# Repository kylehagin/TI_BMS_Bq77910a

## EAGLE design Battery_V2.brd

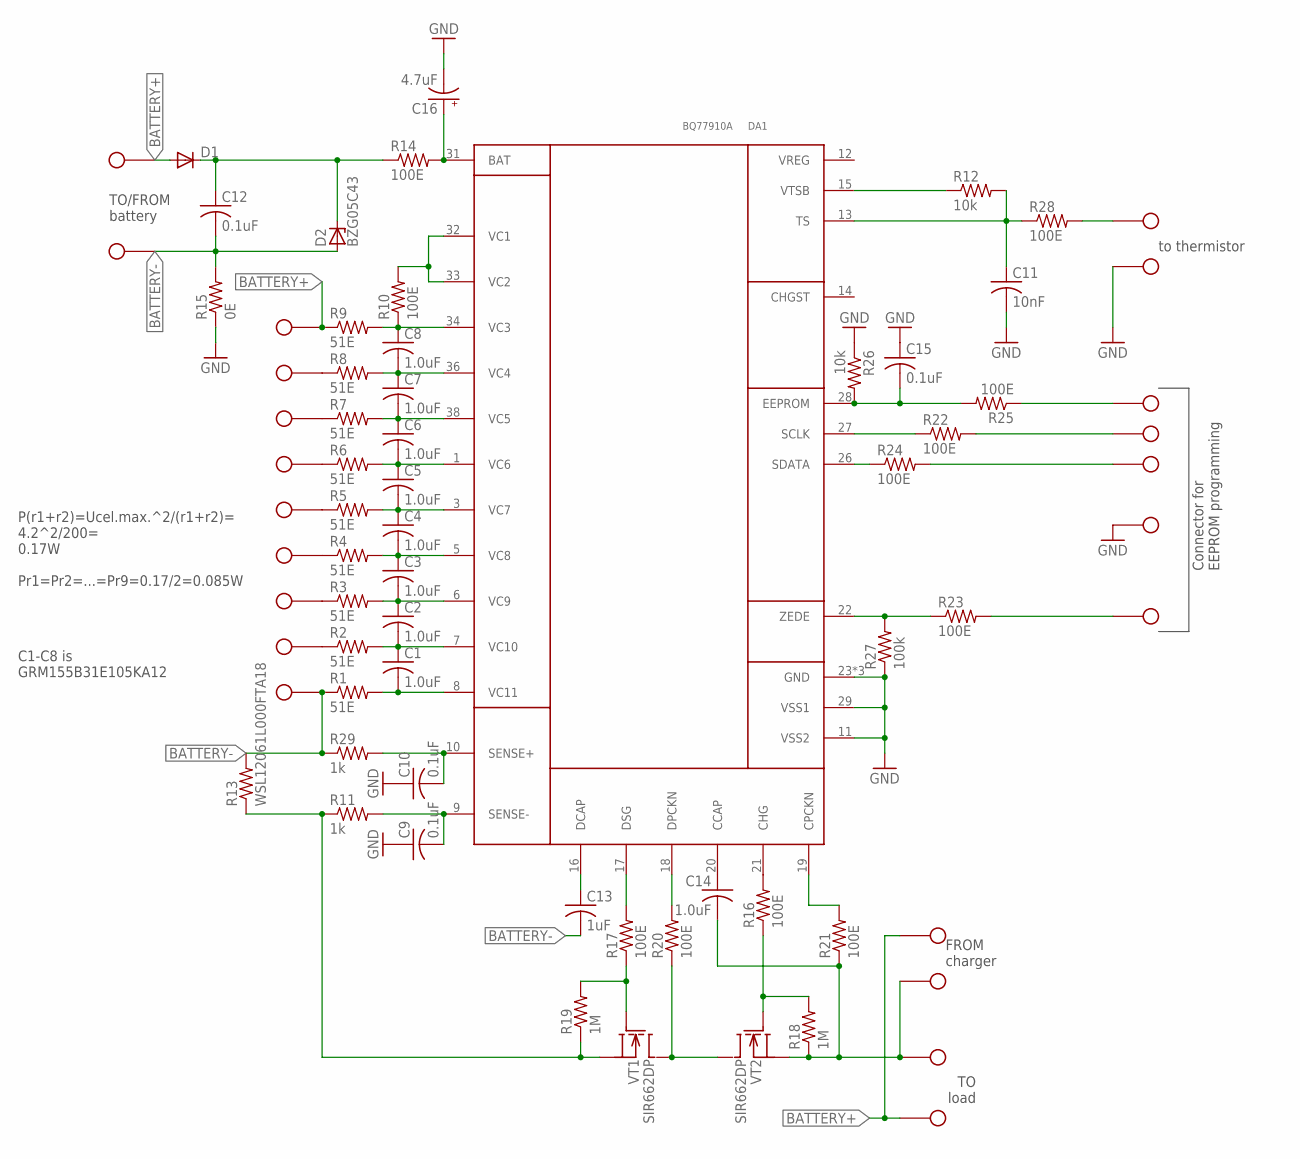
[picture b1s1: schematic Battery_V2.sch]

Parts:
C1, C2, C3, C4, C5, C6, C7, C8: 1.0uF; C0402K
C9, C10: 0.1uF; C0201
C11: 10nF; C0201
C12, C15: 0.1uF; C0402K
C13: 1uF; C0402K
C14: 1.0uF; C0603K
C16: 4.7uF; SMC_P
D1: DIODE-DO-214AC; DO-214AC
D2: BZG05C43; DO-214AC
DA1: BQ77910A; R-PDSO-G38
R1, R2, R3, R4, R5, R6, R7, R8, R9: 51E; M2012
R10, R14, R16, R17, R20, R21, R25: 100E; R0402
R11, R29: 1k; R0201
R12: 10k; R0201
R13: WSL12061L000FTA18; R1206
R15: 0E; R0402
R18, R19: 1M; R0402
R22, R23, R24, R28: 100E; R0201
R26: 10k; R0402
R27: 100k; R0201
VT1, VT2: SIR662DP; POWERPAK_SO8
X1, X2, X3, X4, X5, X6, X7, X8, X9, X10, X11, X21, X23: SOLDER_HOLE24AWG; SOLDER_HOLE_24
X12, X13, X14, X15: SOLDER_HOLE18AWG; SOLDER_HOLE_18
X16, X17, X18, X19, X20: SOLDER_PAD; SOLDER_PAD_SMD

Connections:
BATTERY+: D1.A, R9.1, X1.1, X11.1, X12.1, X15.1
BATTERY-: C12.2, C13.2, D2.A, R1.1, R13.2, R15.2, R29.1, X9.1, X13.1
BATTERY_+: C12.1, D1.C, D2.C, R14.1
GND: C9.1, C10.1, C11.2, C15.1, C16.-, DA1.11 (VSS2), DA1.23 (GND), DA1.24 (GND), DA1.25 (GND), DA1.29 (VSS1), R15.1, R26.1, R27.1, X20.P$1, X21.1
unnamed: C1.2, DA1.8 (VC11), R1.2
unnamed: C1.1, C2.2, DA1.7 (VC10), R2.2
unnamed: C2.1, C3.2, DA1.6 (VC9), R3.2
unnamed: C3.1, C4.2, DA1.5 (VC8), R4.2
unnamed: C4.1, C5.2, DA1.3 (VC7), R5.2
unnamed: C5.1, C6.2, DA1.1 (VC6), R6.2
unnamed: C6.1, C7.2, DA1.38 (VC5), R7.2
unnamed: C7.1, C8.2, DA1.36 (VC4), R8.2
unnamed: C8.1, DA1.34 (VC3), R9.2, R10.1
unnamed: DA1.32 (VC1), DA1.33 (VC2), R10.2
unnamed: C10.2, DA1.10 (SENSE+), R29.2
unnamed: C9.2, DA1.9 (SENSE-), R11.2
unnamed: DA1.21 (CHG), R16.2
unnamed: R11.1, R13.1, R19.1, VT1.S1 (S), VT1.S2 (S), VT1.S3 (S)
unnamed: C16.+, DA1.31 (BAT), R14.2
unnamed: R2.1, X8.1
unnamed: R3.1, X7.1
unnamed: R4.1, X6.1
unnamed: R5.1, X5.1
unnamed: R6.1, X4.1
unnamed: R7.1, X3.1
unnamed: R8.1, X2.1
unnamed: DA1.17 (DSG), R17.2
unnamed: R16.1, R18.2, VT2.G
unnamed: R17.1, R19.2, VT1.G
unnamed: R20.1, VT1.D, VT2.D
unnamed: C14.2, R18.1, R21.1, VT2.S1 (S), VT2.S2 (S), VT2.S3 (S), X10.1, X14.1
unnamed: C14.1, DA1.20 (CCAP)
unnamed: DA1.18 (DPCKN), R20.2
unnamed: DA1.19 (CPCKN), R21.2
unnamed: C13.1, DA1.16 (DCAP)
unnamed: DA1.22 (ZEDE), R23.1, R27.2
unnamed: DA1.26 (SDATA), R24.1
unnamed: DA1.27 (SCLK), R22.1
unnamed: C15.2, DA1.28 (EEPROM), R25.2, R26.2
unnamed: R24.2, X18.P$1
unnamed: R22.2, X17.P$1
unnamed: R25.1, X16.P$1
unnamed: R23.2, X19.P$1
unnamed: DA1.15 (VTSB), R12.1
unnamed: C11.1, DA1.13 (TS), R12.2, R28.1
unnamed: R28.2, X23.1
VREG: DA1.12 (VREG)

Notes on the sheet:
FROM charger
TO/FROM battery
TO load
Connector for EEPROM programming
P(r1+r2)=Ucel.max.^2/(r1+r2)= 4.2^2/200= 0.17W Pr1=Pr2=...=Pr9=0.17/2=0.085W
to thermistor
C1-C8 is GRM155B31E105KA12

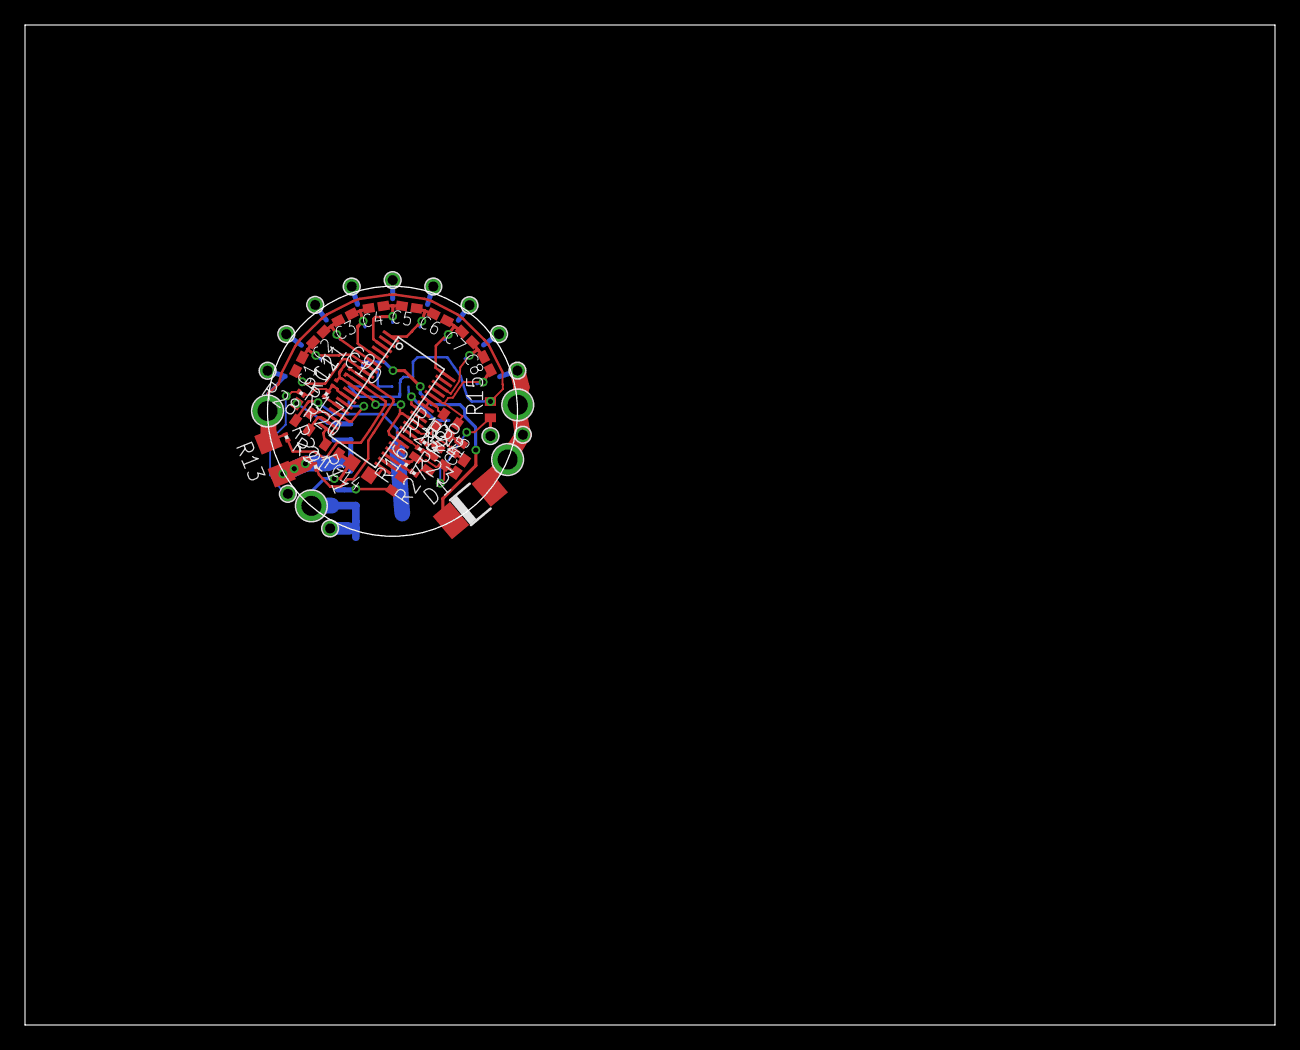
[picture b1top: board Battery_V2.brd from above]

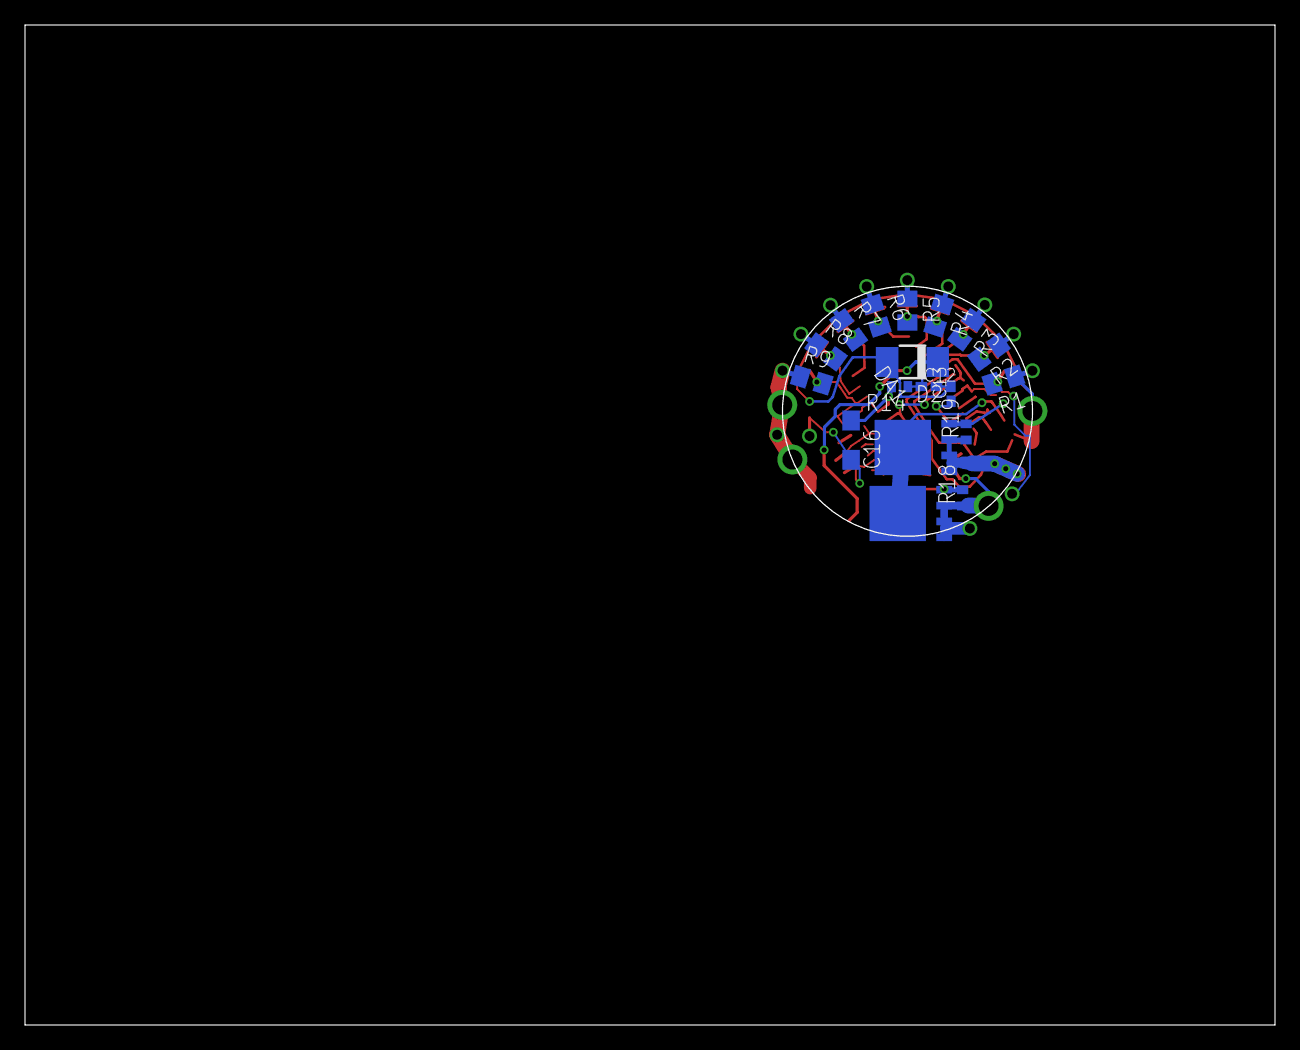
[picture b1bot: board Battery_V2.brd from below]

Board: 2 copper layers, 99.9 x 79.9 mm, 72 parts (18 on the bottom side), 46 nets.
